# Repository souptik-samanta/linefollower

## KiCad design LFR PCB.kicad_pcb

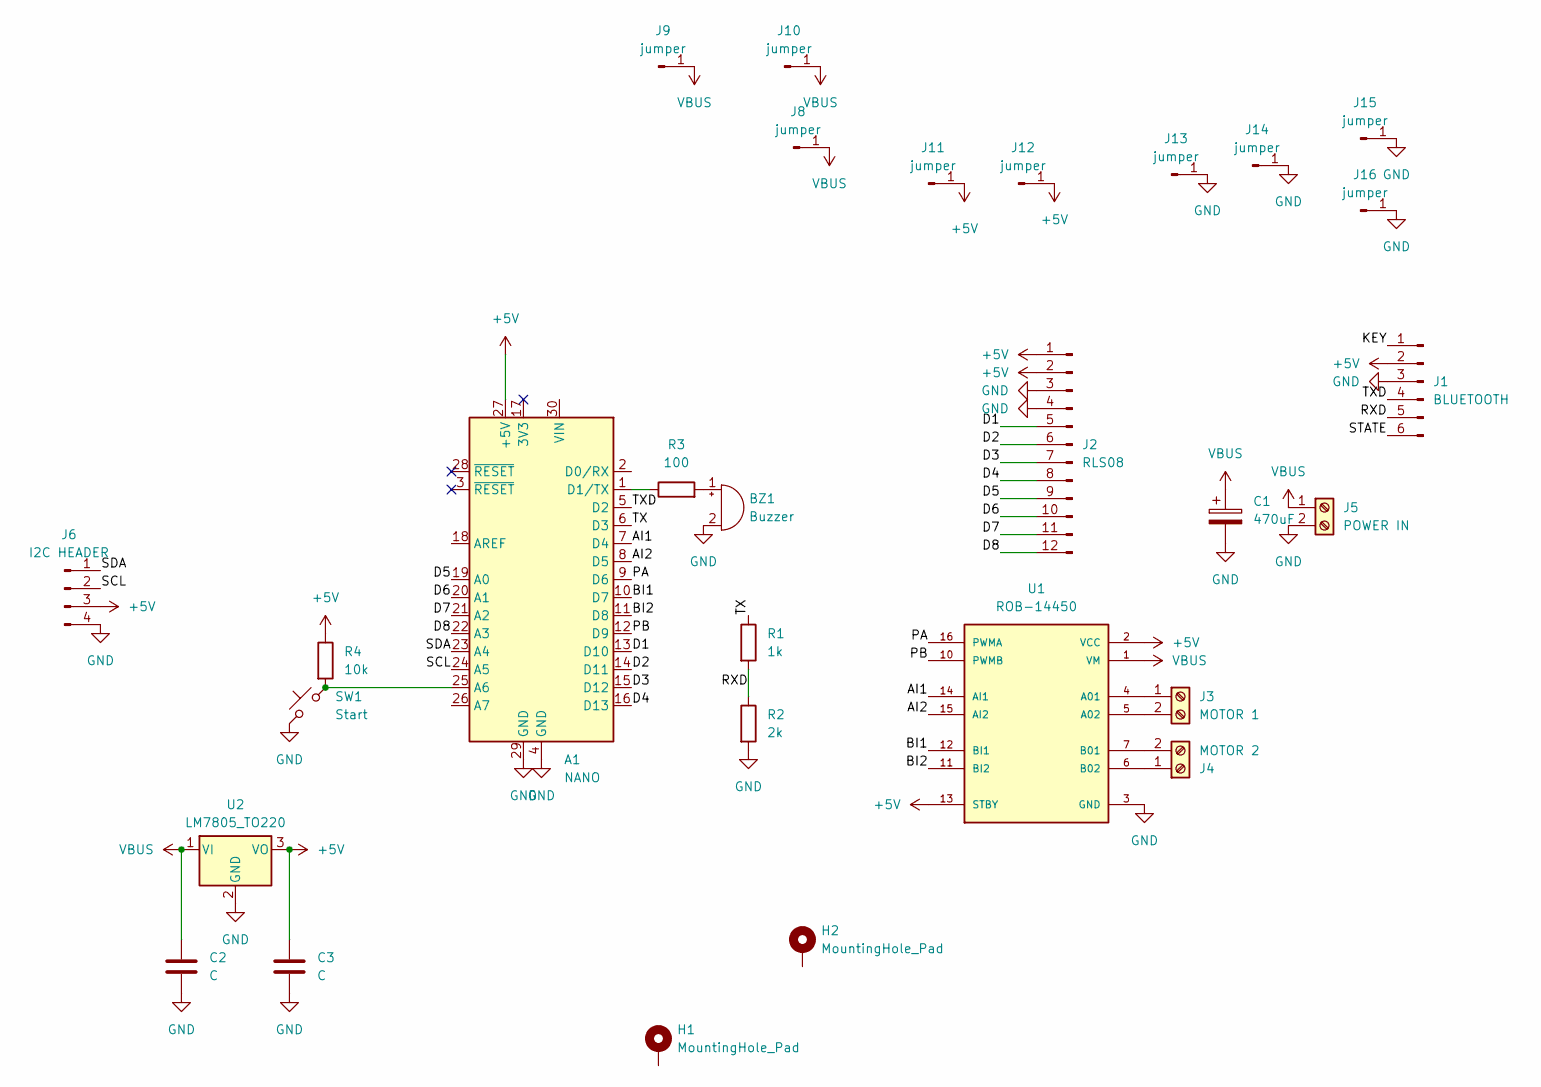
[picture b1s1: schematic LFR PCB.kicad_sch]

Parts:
A1: NANO; Arduino_Nano
BZ1: Buzzer; Buzzer_12x9.5RM7.6
C1: 470uF; CP_Radial_D10.0mm_P5.00mm
C2, C3: C; C_Radial_D8.0mm_H7.0mm_P3.50mm
H1, H2: MountingHole_Pad; MountingHole_3mm_Pad_TopBottom
J1: BLUETOOTH; PinSocket_1x06_P2.54mm_Vertical
J2: RLS08; PinHeader_1x12_P2.54mm_Vertical
J3: MOTOR 1; TerminalBlock_CUI_TB007-508-02_1x02_P5.08mm_Horizontal
J4: MOTOR 2; TerminalBlock_CUI_TB007-508-02_1x02_P5.08mm_Horizontal
J5: POWER IN; TerminalBlock_CUI_TB007-508-02_1x02_P5.08mm_Horizontal
J6: I2C HEADER; PinHeader_1x04_P2.54mm_Vertical
J8, J9, J10, J11, J12, J13, J14, J15, J16: jumper; PinHeader_1x01_P2.54mm_Vertical
R1: 1k; R_Axial_DIN0309_L9.0mm_D3.2mm_P15.24mm_Horizontal
R2: 2k; R_Axial_DIN0309_L9.0mm_D3.2mm_P15.24mm_Horizontal
R3: 100; R_Axial_DIN0309_L9.0mm_D3.2mm_P15.24mm_Horizontal
R4: 10k; R_Axial_DIN0309_L9.0mm_D3.2mm_P15.24mm_Horizontal
SW1: Start; SW_PUSH_6mm
U1: ROB-14450; MODULE_ROB-14450; PARTREV 11-13-17
U2: LM7805_TO220; TO-220-3_Vertical

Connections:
+5V: A1.27 (+5V), C3.1, J1.2, J2.1, J2.2, J6.3, J11.1 (Pin_1_1), J12.1 (Pin_1_1), R4.1, U1.2 (VCC), U1.13 (STBY), U2.3 (VO)
/AI1: A1.7 (D4), U1.14 (AI1)
/AI2: A1.8 (D5), U1.15 (AI2)
/BI1: A1.10 (D7), U1.12 (BI1)
/BI2: A1.11 (D8), U1.11 (BI2)
/D1: A1.13 (D10), J2.5
/D2: A1.14 (D11), J2.6
/D3: A1.15 (D12), J2.7
/D4: A1.16 (D13), J2.8
/D5: A1.19 (A0), J2.9
/D6: A1.20 (A1), J2.10
/D7: A1.21 (A2), J2.11
/D8: A1.22 (A3), J2.12
/KEY: J1.1
/PA: A1.9 (D6), U1.16 (PWMA)
/PB: A1.12 (D9), U1.10 (PWMB)
/RXD: J1.5, R1.2, R2.1
/SCL: A1.24 (A5), J6.2
/SDA: A1.23 (A4), J6.1
/STATE: J1.6
/TX: A1.6 (D3), R1.1
/TXD: A1.5 (D2), J1.4
GND: A1.4 (GND), A1.29 (GND), BZ1.2 (-), C1.2, C2.2, C3.2, J1.3, J2.3, J2.4, J5.2, J6.4, J13.1 (Pin_1_1), J14.1 (Pin_1_1), J15.1 (Pin_1_1), J16.1 (Pin_1_1), R2.2, SW1.1, U1.3 (GND), U1.8 (GND), U1.9 (GND), U2.2 (GND)
unnamed: A1.25 (A6), R4.2, SW1.2
unnamed: A1.1 (D1/TX), R3.1
unnamed: BZ1.1 (+), R3.2
unnamed: J3.1, U1.4 (A01)
unnamed: J3.2, U1.5 (A02)
unnamed: J4.1, U1.6 (B02)
unnamed: J4.2, U1.7 (B01)
VBUS: C1.1, C2.1, J5.1, J8.1 (Pin_1_1), J9.1 (Pin_1_1), J10.1 (Pin_1_1), U1.1 (VM), U2.1 (VI)

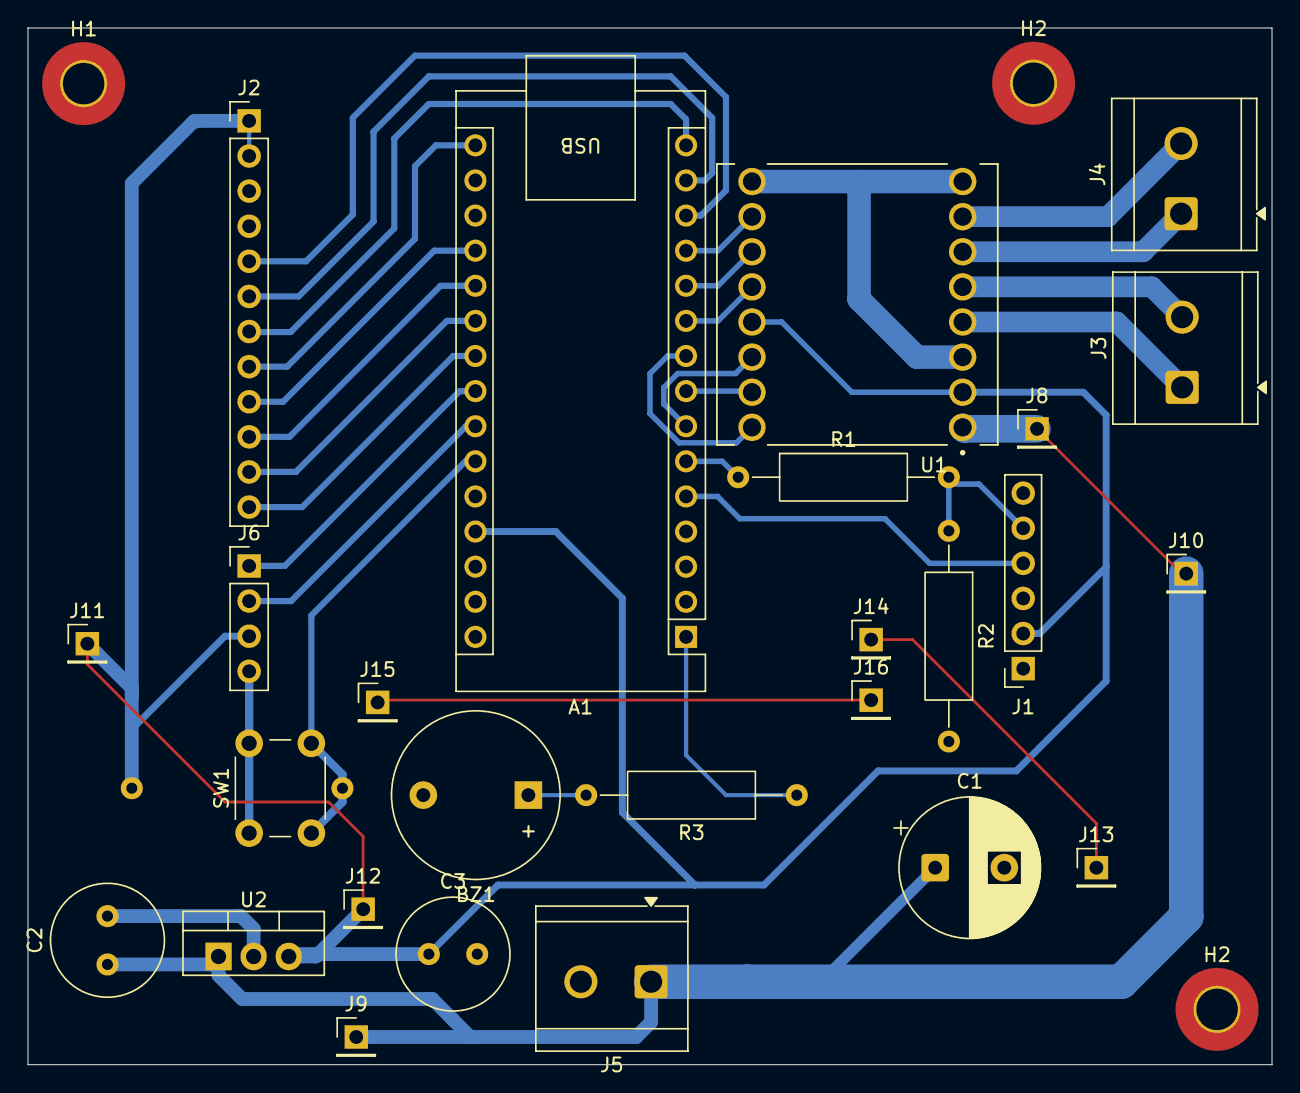
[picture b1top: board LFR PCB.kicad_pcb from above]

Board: 2 copper layers, 90.0 x 75.0 mm, 30 parts (1 on the bottom side), 29 nets.

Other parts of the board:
H2#2: MountingHole_Pad; MountingHole_3mm_Pad_TopBottom
